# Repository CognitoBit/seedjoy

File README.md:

# SeedJoy

Game-controller firmware for the **Seeed Studio XIAO nRF52840**, with a zero-install web
configurator. The board shows up as a standard HID **joystick** over **USB** or **Bluetooth LE**,
with up to **56 buttons** (74HC165 shift registers) and **4 analog axes**.

> **Board:** Seeed Studio XIAO nRF52840, the *non-Sense* board, using the **"Seeed nRF52 Boards"**
> Arduino core (FQBN `Seeeduino:nrf52:xiaonRF52840`). The mbed-based Seeed core and the Sense
> board definition are not supported by this build.

---

## Features

- **56 buttons** from up to 7 daisy-chained 74HC165s on 3 pins (D6/D7/D8), debounced
- **4 analog axes** (A0–A3, 12-bit) with calibration, deadzone, expo curve, smoothing, invert
- **USB HID or BLE HID**, chosen at boot by pin D9
- **Web configurator** (Chrome/Edge): connect over **Web Serial** (USB cable, either mode) or
  **WebBluetooth** (BLE mode), read and write the full config, calibrate axes, and watch live
  button states
- **Persistent config** in on-chip flash (LittleFS, CRC32-checked)
- **Ghost-input protection**: HID input is held off for 60 s after each BLE connection
- **Battery level** reported through the BLE Battery Service (LiPo on the XIAO's BAT pads)
- Force feedback (USB PID) exists as an experimental, **off-by-default** build option, see
  [docs/ffb-plan.md](docs/ffb-plan.md)

---

## Hardware

### Parts

| Part | Qty | Notes |
|------|-----|-------|
| Seeed Studio XIAO nRF52840 | 1 | Non-Sense |
| 74HC165 shift register | 1–7 | 8 buttons each |
| 10 kΩ resistor | 1 per button | Pull-up on each 74HC165 input |
| Buttons / switches | up to 56 | Input → GND |
| 10 kΩ linear potentiometer | 0–4 | Optional axes |
| Switch or jumper on D9 | 1 | Only to boot into BLE mode |
| 3.7 V single-cell LiPo | 0–1 | Optional, for wireless use |

**Everything runs at 3.3 V.** Power the 74HC165s, pull-ups and pots from the XIAO's **3V3** pin.
XIAO pins are not 5 V tolerant.

### Pin map

| XIAO pin | Port | Function |
|----------|------|----------|
| A0–A3 (D0–D3) | P0.02, P0.03, P0.28, P0.29 | Axes 0–3 (X, Y, Z, Rz), **disabled by default** |
| D4, D5, D10 | P0.04, P0.05, P1.15 | Optional direct GPIO buttons, disabled by default |
| **D6** | P1.11 | 74HC165 **data**: QH (pin 9) of the chip nearest the XIAO |
| **D7** | P1.12 | 74HC165 **clock**: CLK (pin 2) of every chip |
| **D8** | P1.13 | 74HC165 **load**: SH/LD (pin 1) of every chip |
| **D9** | P1.14 | **Mode select**: open = USB, GND at boot = BLE |
| RGB LED | P0.26 red, P0.06 blue | Red: booting / error blinks. Blue: USB mounted, or BLE connected |
| BAT+/BAT− pads | n/a | LiPo (underside) |

### Shift-register wiring (74HC165)

```
            far end                                          nearest XIAO
 3V3 → SER[Chip 1]QH → SER[Chip 2]QH → … → SER[Chip 7]QH ──────────► D6
        buttons 1–8    buttons 9–16          buttons 49–56

 D7 → CLK (pin 2) of every chip        D8 → SH/LD (pin 1) of every chip
 3V3 → VCC (16) of every chip           GND → GND (8) and CLK INH (15) of every chip
```

- Chain with **QH (pin 9) → next chip's SER (pin 10)**. Do not use /QH (pin 7); it's inverted.
- The far-end chip's SER goes to **3V3** (so unused chain positions read as released). Buttons
  1–8 are on that chip: input A = button 1, input H = button 8.
- Each input gets a **10 kΩ pull-up to 3V3**, and the switch goes from the input to **GND**.
  Released reads HIGH, pressed reads LOW. The default *Invert Logic = on* reports pressed as 1.
- Fewer than 7 chips is fine. Set **Number of chips** in the configurator to match what's fitted,
  because numbering always starts at the far-end chip.

Full wiring guide with the 74HC165 pinout: [docs/hardware.md](docs/hardware.md).

**Test board:** a ready-to-fab KiCad board that exercises everything (74HC165 + 8 buttons, chain
header, DIP switches, on-board thumbstick, external analog header) is in [pcb/](pcb/). See
[pcb/README.md](pcb/README.md) for the bring-up checklist and [pcb/BOM.md](pcb/BOM.md) for
India-sourced parts.

---

## Build and flash

### 1. Install the board support package

Arduino IDE 2.x or [arduino-cli](https://arduino.github.io/arduino-cli/latest/installation/).
Add this board-manager URL:

```
https://files.seeedstudio.com/arduino/package_seeeduino_boards_index.json
```

Install **Seeed nRF52 Boards** (tested with **1.1.10**). Do *not* install the "mbed-enabled"
package. No extra libraries are needed: TinyUSB, Bluefruit and LittleFS ship with the core.
Don't install a separate "Adafruit TinyUSB" from Library Manager, since it can shadow the
core's copy.

```bash
arduino-cli config add board_manager.additional_urls \
  https://files.seeedstudio.com/arduino/package_seeeduino_boards_index.json
arduino-cli core update-index
arduino-cli core install Seeeduino:nrf52
```

### 2. Compile

```bash
cd firmware/seedjoy
./compile.sh
```

This produces `build/seedjoy.uf2` (drag-and-drop image), `build/seedjoy.ino.zip` (serial DFU
package) and `build/seedjoy.ino.hex`. `compile.sh` uses `arduino-cli` from your `PATH` (or
`~/bin/arduino-cli`).

In the Arduino IDE: open `firmware/seedjoy/seedjoy.ino`, select **Tools → Board → Seeed nRF52
Boards → Seeed XIAO nRF52840** (not "Sense"), then Upload.

### 3. Flash

**Option A: UF2 drag-and-drop (simplest)**

1. Connect the XIAO by USB-C (use a data cable).
2. **Double-tap the RESET button.** A USB drive appears (the UF2 bootloader).
3. Copy `build/seedjoy.uf2` onto that drive. The board reboots into SeedJoy.

**Option B: serial upload**

```bash
./upload.sh              # finds /dev/cu.usbmodem* (macOS) or /dev/ttyACM* (Linux)
PORT=/dev/cu.usbmodem1101 ./upload.sh   # or pick the port yourself
```

Or in the IDE, press Upload. If the port isn't found, double-tap RESET and retry.

### Apple Silicon Macs without Rosetta

Seeed's core 1.1.10 ships **x86_64-only** `arm-none-eabi-gcc` 9-2019q4 and `adafruit-nrfutil`,
and Arduino's `ctags` is x86_64-only too. Without Rosetta, compiling fails with
`bad CPU type in executable`. Either install Rosetta (`softwareupdate --install-rosetta`), or
point the scripts at native tools:

```bash
# 1. Native ARM toolchain (Arm GNU Toolchain, darwin-arm64 tarball, e.g. 13.3.rel1)
#    https://developer.arm.com/downloads/-/arm-gnu-toolchain-downloads
# 2. adafruit-nrfutil from PyPI
python3 -m venv ~/.venvs/nrfutil && ~/.venvs/nrfutil/bin/pip install adafruit-nrfutil
# 3. Arduino's ctags fork, built natively
git clone --depth 1 --branch 5.8-arduino11 https://github.com/arduino/ctags.git
cd ctags && grep -rl __unused__ . | grep -E '\.(c|h)$' | xargs sed -i '' 's/__unused__/CTAGS_UNUSED/g'
./configure && make && cd ..

# then:
ARM_GCC_BIN=/path/to/arm-gnu-toolchain-13.3.rel1-darwin-arm64-arm-none-eabi/bin \
NRFUTIL=~/.venvs/nrfutil/bin/adafruit-nrfutil \
CTAGS_DIR=/path/to/ctags \
./compile.sh

NRFUTIL=~/.venvs/nrfutil/bin/adafruit-nrfutil ./upload.sh   # or just use the UF2 drive
```

This is how the current tree was build-verified: gcc 13.3.rel1, 148 KB flash (18 %), 20.6 KB RAM
(8 %). The "`_close is not implemented`"-style linker warnings from newer newlib are harmless.

---

## First boot and mode selection

D9 is sampled **once at boot** (internal pull-up):

| D9 at reset | Mode | What the host sees |
|-------------|------|--------------------|
| Nothing connected | **USB** | USB joystick "SeedJoy" + a serial port (VID `0x239A`, PID `0x80F4`) |
| Tied to GND | **BLE** | BLE HID joystick advertising as "SeedJoy" (plus the serial port if USB is plugged in) |

To change mode, change D9 and press RESET. The `mode` field in the saved config is currently
informational only, and D9 always decides.

In USB mode the serial port drops once and reappears about a second after boot. That's expected:
the firmware forces the host to re-enumerate so the joystick interface appears.

Boot log (Serial Monitor, 115200 baud) prints the selected mode, enabled axes and the
shift-register setup.

### Default configuration

| Setting | Default |
|---------|---------|
| Shift registers | **enabled**, 7 chips, D6/D7/D8, Invert Logic **on** |
| Axes 0–3 | **disabled** (enable only the ones you've wired) |
| Direct GPIO buttons | disabled |
| Device name | `SeedJoy` |

With a full 7-chip chain, a board wired as above works with no configuration at all: SR buttons
appear as HID buttons 1–56. With fewer chips, the fitted chips first show up at the top of the
range (one chip on D6 = buttons 49–56) until you set *Number of chips* in the configurator. Nothing
reads as stuck pressed, as long as the far-end SER is tied to 3V3.

> **Upgrading from an older build?** A config already saved on the board keeps its old values.
> In particular the old default was *Invert Logic = off*, which makes every idle button read as
> pressed with pull-up wiring. Open the configurator, **Read from Device**, tick **Invert Logic**,
> and **Write to Device**.

### Testing it

- **Windows:** `joy.cpl` (Game Controllers), select SeedJoy, then Properties
- **Linux:** `jstest /dev/input/js0`
- **Any OS:** https://hardwaretester.com/gamepad in Chrome

`joy.cpl` and browser gamepad testers display **only the first 32 buttons**. The configurator's
Button Mapping tab shows all 64. Games and SDL/DirectInput apps read the full report.

### BLE mode and the 60-second window

Every time a BLE central connects (your PC *or* the web configurator), the firmware holds off
HID input for **60 seconds** so floating or unconfigured inputs can't spam the host while you
configure. The blue LED lights while connected.

- After pairing with your PC, expect **no input for the first minute** of each connection.
- Send `H` over the serial port to enable HID immediately, or `C` to restart the window.
- Press and hold a button on D9 (to GND) during the window to keep it open. A switch left
  closed since boot is ignored for this, so a permanent BLE jumper won't block HID.

Pair from the OS Bluetooth settings as you would any controller. If pairing gets stuck, remove
"SeedJoy" from the OS device list and reset the board.

---

## Web configurator

### Open it

WebBluetooth and Web Serial need a secure context. `http://localhost` counts as one:

```bash
cd configurator
python3 -m http.server 8000
# open http://localhost:8000 in Chrome or Edge (Firefox/Safari have neither API)
```

### Connect

Pick **🔌 USB Serial** or **📡 Bluetooth** at the top, then **Connect Device**.

| Mode | Transport | Works when the firmware is in |
|------|-----------|-------------------------------|
| USB Serial (Web Serial, 115200 baud) | USB cable | USB mode **or** BLE mode (with cable plugged in) |
| Bluetooth (WebBluetooth) | Wireless GATT | BLE mode only |

The Bluetooth picker filters on names starting with `SeedJoy`. If you rename the device, keep
that prefix.

### Workflow

1. **Read from Device** loads the board's current config into the UI. Always do this first.
2. **Pin Config** tab: shift registers (enable, chip count, pins, Invert Logic), axis and GPIO
   button enables.
3. **Axis Calibration** tab: live readout, set min/center/max, deadzone, curve, smoothing.
4. **Button Mapping** tab: 56 indicators light up live as you press buttons. Over serial the
   firmware streams states at 20 Hz; over BLE they arrive as GATT notifications.
5. **Write to Device** saves to flash. Shift-register and axis changes apply immediately, no
   reboot needed.

Pin values in the configurator and in the JSON protocol are **Arduino pin numbers**
(D0–D10 = 0–10); see [docs/protocol.md](docs/protocol.md#pin-numbers).

> ⚠️ Enable only axes and buttons that are physically wired. A floating pin reads noise and
> produces phantom input.

---

## Serial protocol

115200 baud, newline-terminated text commands. Available in both USB and BLE mode.

| Command | Response | Purpose |
|---------|----------|---------|
| `ping` | `{"type":"pong"}` | Connection check |
| `read_config` | `{"type":"config","data":{…}}` | Full config as JSON |
| `write_config:{JSON}` | `{"type":"status","success":true\|false,"message":"…"}` | Apply and save config |
| `stream_buttons` | `{"type":"buttons","data":{"states":[b0,…,b7]}}` at 20 Hz | Start live button stream (8 bytes = 64 bits) |
| `stop_stream` | `{"type":"status",…}` | Stop the button stream |
| `stream_axes` | `{"type":"axes","data":{"raw":[4],"processed":[4]}}` at 20 Hz | Live axis values (the calibration tab uses this over USB) |
| `stop_axes` | `{"type":"status",…}` | Stop the axis stream |
| `C` | text | BLE mode: (re)enter the config window, HID off |
| `H` | text | BLE mode: enable HID now |
| `?` | text | Help |

The BLE GATT config service and message formats are described in [docs/protocol.md](docs/protocol.md).

---

## HID report

One 16-byte input report. Usage page Generic Desktop, usage **Joystick**. Over USB it has no
report ID; over BLE it's Report ID 1.

```
Bytes 0–7    Axes X, Y, Z, Rz   int16 little-endian, −32767 … 32767
Bytes 8–15   Buttons 1–64       1 bit each (SR-only mode uses buttons 1–56)
```

Button bit *n* is HID button *n+1*. In SR-only mode, SR input *n* maps to bit *n*. If any direct
GPIO button is enabled, SR buttons move up by 16 (the 16 GPIO slots come first), so a 7-chip
chain's last 8 buttons no longer fit in the 64-bit report. For 56 buttons, use SR only.

---

## Troubleshooting

**Every button shows as pressed.** Invert Logic is off (a config saved by an older build). Read →
tick *Invert Logic* → Write.

**Buttons shifted / wrong numbers.** The configured chip count doesn't match the chips fitted, or
the chain is wired through /QH (pin 7) instead of QH (pin 9).

**No shift-register buttons at all.** Check D6/D7/D8 and 3V3/GND to every chip, CLK INH (pin 15)
to GND, and SR *enabled* in the config. The boot log prints the SR settings. Configs written by
older configurator builds stored invalid pin numbers (e.g. 43/44/45 for D6/D7/D8). The firmware
now repairs these at boot and logs `Repaired invalid pin numbers in stored config`.

**USB mode: no joystick, only a serial port.** Use a data cable, and check the boot log says
`USB HID initialized successfully`. On Windows, look in `joy.cpl`, not only Device Manager.

**BLE mode: connected but no input.** Wait out the 60 s window, or send `H` over serial.

**Can't find the device in the Bluetooth picker.** Check D9 was on GND at reset (the boot log
says `Selected mode: BLE`), and that the name still starts with `SeedJoy`.

**Axes drift or jitter.** Calibrate, raise the deadzone or smoothing, add 100 nF from wiper to GND.

**Config lost after reboot.** After a write the log should say `Config saved to Flash`; on the next boot, `Config loaded from Flash`. Anything else (`CRC mismatch`, `size mismatch`) means the stored config was rejected and defaults were used.

**Compile fails with `bad CPU type in executable`.** See
[Apple Silicon Macs without Rosetta](#apple-silicon-macs-without-rosetta).

More: [docs/troubleshooting.md](docs/troubleshooting.md).

---

## Project layout

```
firmware/seedjoy/
├── seedjoy.ino          setup/loop, D9 mode select, BLE config window, serial commands
├── config.h             DeviceConfig struct, default pins
├── axes.*               ADC read, calibration, deadzone, curves, smoothing
├── buttons.*            GPIO + shift-register buttons, debounce, 64-bit state
├── shift_registers.*    74HC165 bit-bang reader
├── usb_hid.*            TinyUSB joystick (16-byte report)
├── ble_hid.*            Bluefruit BLE HID joystick + battery service
├── ble_config.*         GATT config / monitor / calibration service
├── storage.*            LittleFS config persistence, CRC32
├── ffb_*                Experimental force feedback (ENABLE_FFB=0 by default)
├── compile.sh / upload.sh
firmware/tests/          Host-side unit tests for the FFB engine (bash run_tests.sh)
configurator/            Static web app: index.html, app.js, serial.js, ble.js, config.js, …
docs/                    hardware.md, protocol.md, troubleshooting.md, getting-started.md, FFB docs
```

---

## Status and known limitations

- The current tree **compiles** for `Seeeduino:nrf52:xiaonRF52840` (core 1.1.10) and the host
  unit tests pass. The fixes in this revision (USB re-enumeration, LED polarity, D9 handling,
  configurator pin numbering, SR polarity default, stored-pin repair) have **not yet been verified on a physical
  board**.
- BLE config characteristics are unauthenticated (anyone in range can write config). See
  [docs/audit.md](docs/audit.md) H2.
- `mode` in the config is ignored (D9 decides), and `autoSleep` isn't implemented yet.
- Mixing GPIO buttons with a full 7-chip chain drops the last 8 SR buttons (see HID report).

## Roadmap

- [ ] Configuration import/export as a JSON file
- [ ] Rotary encoders
- [ ] 8 axes via external ADC (ADS1115)
- [ ] Button matrices
- [ ] OTA firmware update via BLE DFU

## License

MIT, see [LICENSE](LICENSE).

## Credits

Inspired by [FreeJoy](https://github.com/FreeJoy-Team/FreeJoy) by Alexandr Yaroshenko.

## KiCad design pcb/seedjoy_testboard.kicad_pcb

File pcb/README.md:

# SeedJoy Test Board rev A: bring-up checklist

Board: `seedjoy_testboard.kicad_pro` (KiCad 10). Fab files: `seedjoy_testboard_gerbers.zip`.
Parts: [BOM.md](BOM.md), with jumper settings.

## Before ordering the PCB

- [ ] Buy the KY-023 / PS2 joystick module first. Desolder the stick and measure it: the 3 pins of
      each pot are **2.5 mm apart**, and the two pot rows are **8.73 mm from the stick centre**
      (Alps RKJXV1224005 pattern). If your clone differs, stop and report it before ordering.
- [ ] **1:1 paper-fit test** (catches a mirrored pattern and body pegs that calipers miss):
      in KiCad, File → Print F.Cu + Edge.Cuts at **100 % scale** and check the board width
      (130 mm) with a ruler. Push the desoldered stick's legs through the printed pads (from the
      printed side, stick on top). It must sit **flat**: no plastic pegs hitting the paper, and
      the X-pot row on top, the Y-pot column on the right, the switch legs at the bottom. The legs
      should protrude ≥ 2.4 mm below the body to solder through a 1.6 mm board.
      Repeat for the DIP switch, one tactile switch, RN1 and the XIAO socket pitch.

## Before powering up (bare board, multimeter)

- [ ] **3V3 to GND is not a short**: > 1 kΩ on the J2 3V3 pin vs GND.
- [ ] No XIAO fitted yet. Check continuity **J2 pin 3 (3V3) → U1 socket pin 16** and
      **J2 pin 2 (GND) → U1 socket pin 8**.

## Assembly order

1. IC socket (notch towards the XIAO side of the silkscreen), RN1 (dot = pin 1 = square pad), R1, C1.
2. DIP switch (switch 1 next to the "1 D4" label), 8 tactile switches.
3. Female headers: J1/J2 (XIAO), J3 (external analog). Male headers: J4, J5, J6, J7, J8, J9.
4. Thumbstick U2 last. Insert the **74HC165** into its socket, notch matching.
5. Plug in the XIAO **with USB-C towards the top edge** ("USB up" silkscreen).

## First power-up (no jumpers fitted, all DIP switches OFF)

1. Flash firmware: double-tap RESET → `XIAO-BOOT` drive → copy `firmware/seedjoy/build/seedjoy.uf2`.
2. After about 1 s the **blue LED is on** and the red LED is off (USB HID mounted). A red LED
   blinking 5× means USB HID failed.
3. The OS lists a game controller named **SeedJoy** (`joy.cpl` on Windows, `jstest` on Linux).
4. The serial port drops and reappears once at boot (USB re-enumeration), so a terminal usually
   misses the boot log. Open it afterwards and send `?`: the command help confirms the firmware
   is alive.

## Configure (configurator → USB Serial → Connect → **Read from Device**)

- [ ] **Pin Config → Number of chips = 1**, Invert Logic **ticked** → **Write to Device**.
      (The firmware default is 7 chips. With 7, this board's buttons show up as HID 49–56.)
- [ ] **Button Mapping** tab: BTN1…BTN8 light up as indicators 1…8. Idle = all dark.
      Use this tab as the ground truth. **Windows `joy.cpl` and browser gamepad testers only
      show the first 32 buttons**, so at the default 7 chips (HID 49–56) the board would look dead
      there. That's another reason to set chips = 1 first.

## Analog

1. Fit **J8 on 1-2** (X from the on-board stick) and **J4 on row 1** (X → A0).
   Fit **J9 on 1-2** and **J5 on row 2** (Y → A1). *Never put J4 and J5 on the same row.*
2. Pin Config: enable **Axis 0** (pin A0) and **Axis 1** (pin A1) → Write.
3. Axis Calibration: raw ≈ 2048 at rest. PS2-style sticks usually **don't reach 0 / 4095** at
   the ends (often ~300–3800). That's normal, and the calibration exists for it:
   run min/center/max → Write.
4. External sensor: move J8 (or J9) to **2-3**, plug the sensor into **J3** (GND, 3V3, X, Y, SW).
   **3.3 V only.** Use a 3.3 V-capable hall sensor (e.g. SS49E / DRV5055A1 at 3.3 V).
5. **J6 on** means the stick push button (on-board or J3 SW) acts as BTN8.

## GPIO buttons and mode (DIP switch SW9)

- [ ] Enable GPIO buttons 0–2 (pins D4, D5, D10) in the configurator → Write. DIP 1–3 ON = pressed.
      **While any GPIO button is enabled, the shift-register buttons move to HID 17+.**
- [ ] **DIP 4 ON + reset** boots BLE mode (`Selected mode: BLE`). Pair "SeedJoy" from the OS.
      Input starts **60 s after each connection** (send `H` over serial to skip).
      DIP 4 back OFF + reset returns to USB mode.

## Chaining your own 74HC165 board (J7)

J7 = 3V3, GND, CLK (D7), LOAD (D8), SER-in. Your chain's last QH → J7 pin 5.
Your N chips become HID 1…8N and this board's buttons follow. Set Number of chips = N + 1.

## Known cosmetic warnings in KiCad

The DRC shows `lib_footprint_mismatch` (library metadata) and 3 "field differs" parity notes.
They don't affect fabrication. Tools → Update Footprints from Library / Update PCB from
Schematic clears them.

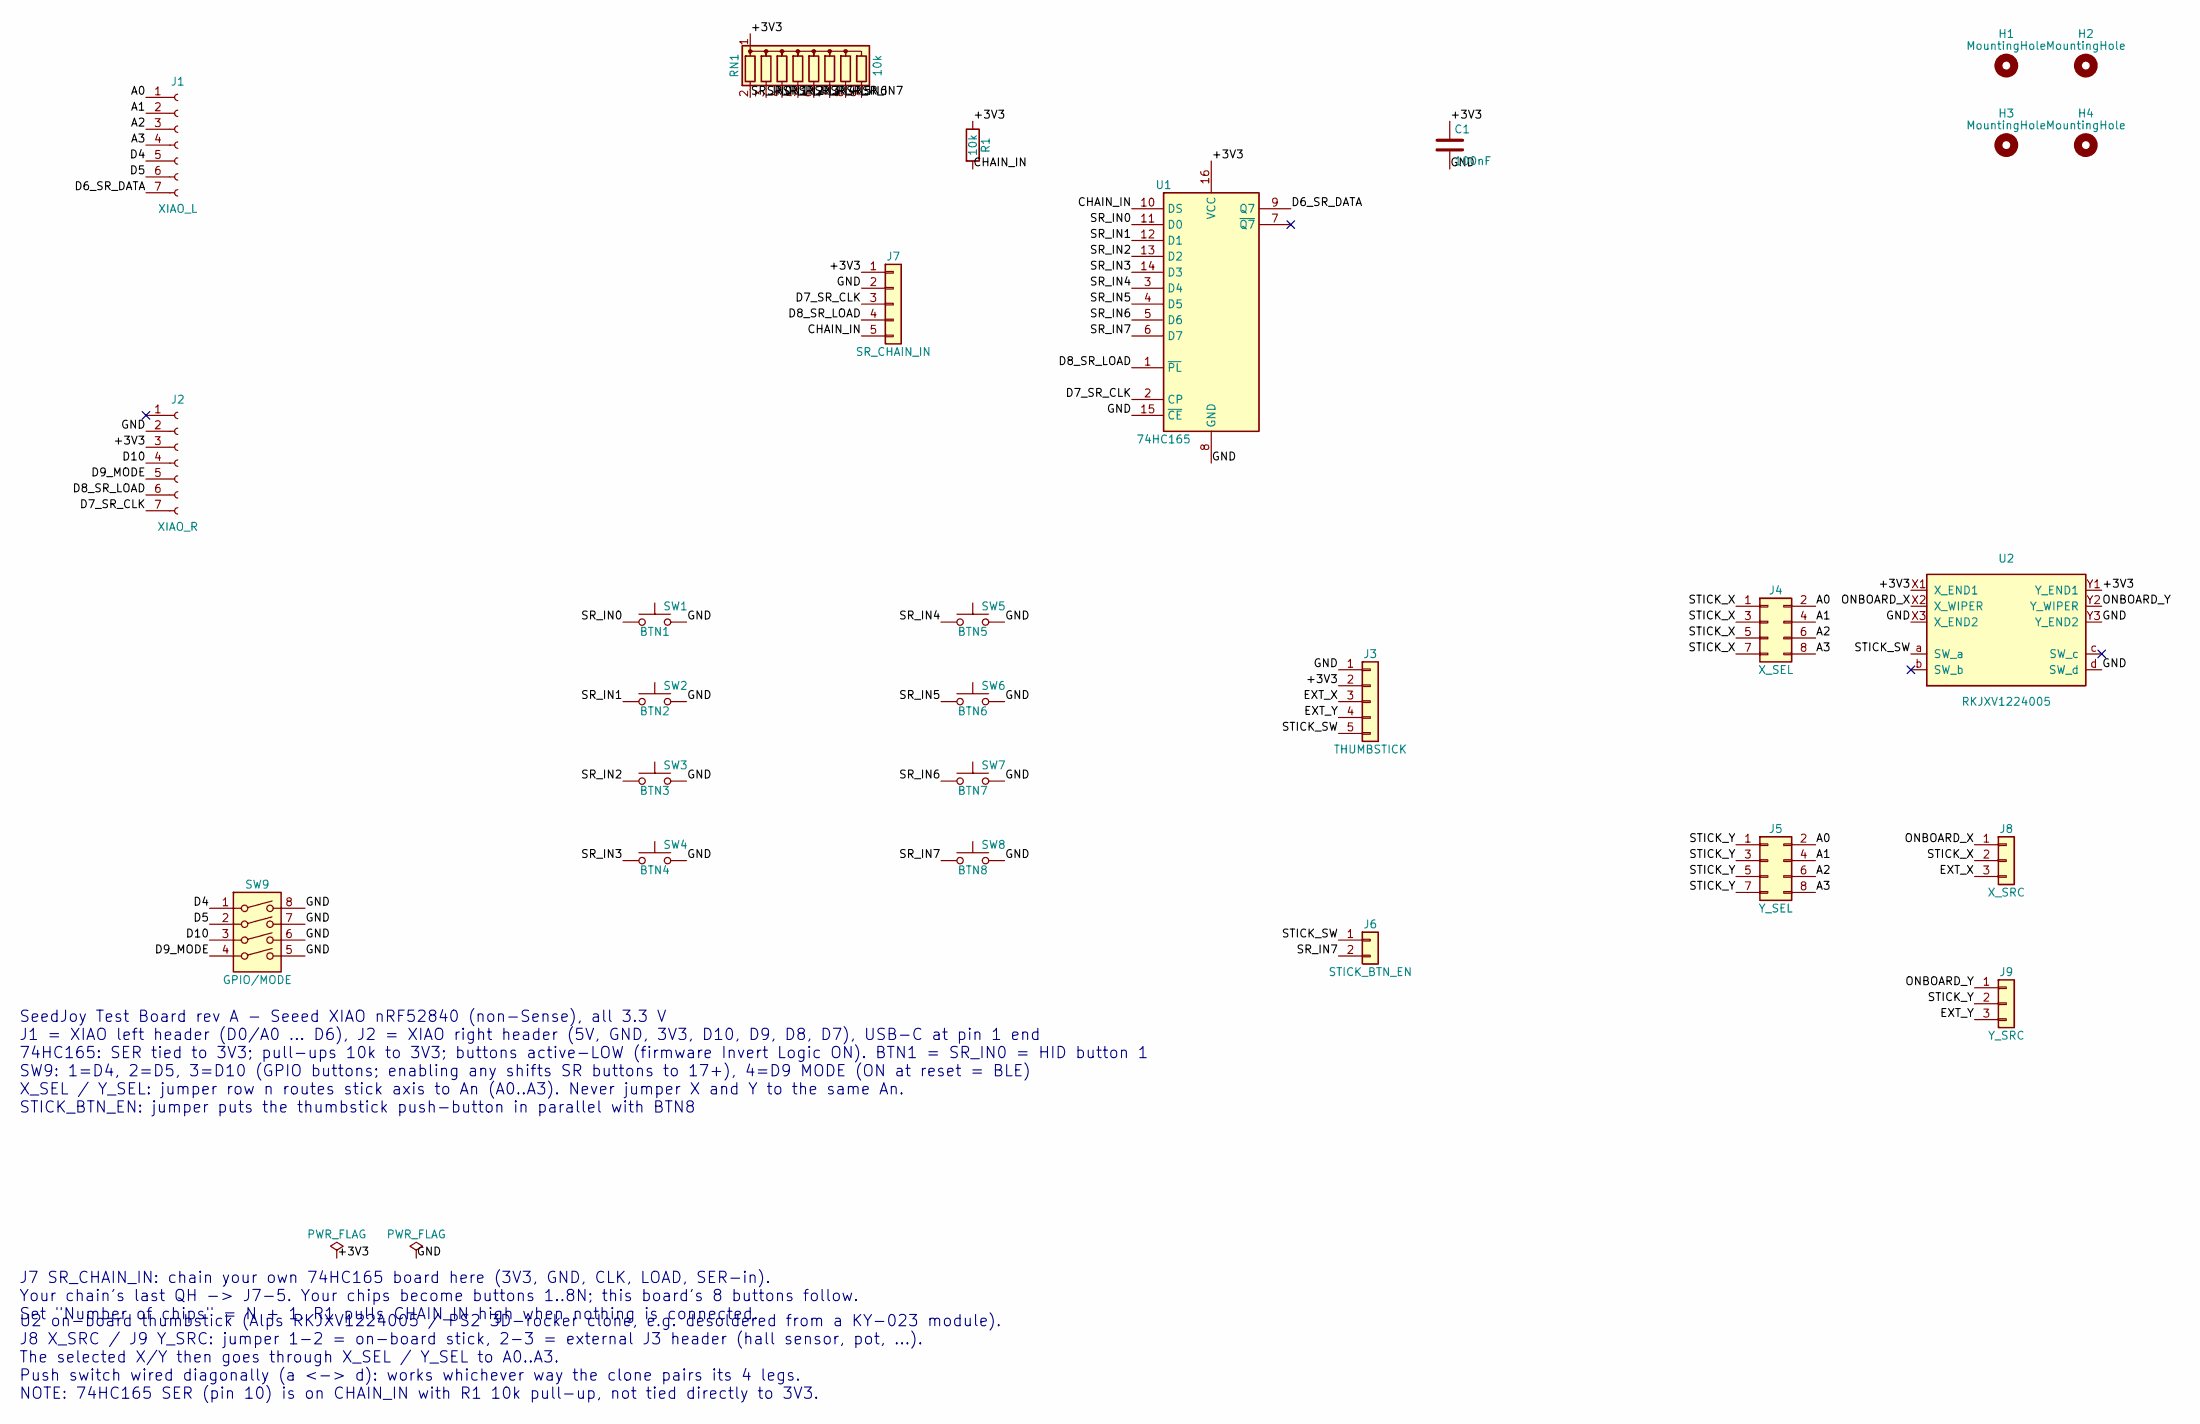
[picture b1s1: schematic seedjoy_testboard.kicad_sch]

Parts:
C1: 100nF; C_Disc_D5.0mm_W2.5mm_P5.00mm
H1, H2, H3, H4: MountingHole; MountingHole_3.2mm_M3
J1: XIAO_L; PinSocket_1x07_P2.54mm_Vertical
J2: XIAO_R; PinSocket_1x07_P2.54mm_Vertical
J3: THUMBSTICK; PinHeader_1x05_P2.54mm_Vertical
J4: X_SEL; PinHeader_2x04_P2.54mm_Vertical
J5: Y_SEL; PinHeader_2x04_P2.54mm_Vertical
J6: STICK_BTN_EN; PinHeader_1x02_P2.54mm_Vertical
J7: SR_CHAIN_IN; PinHeader_1x05_P2.54mm_Vertical
J8: X_SRC; PinHeader_1x03_P2.54mm_Vertical
J9: Y_SRC; PinHeader_1x03_P2.54mm_Vertical
R1: 10k; R_Axial_DIN0207_L6.3mm_D2.5mm_P10.16mm_Horizontal
RN1: 10k; R_Array_SIP9
SW1: BTN1; SW_PUSH_6mm_H5mm
SW2: BTN2; SW_PUSH_6mm_H5mm
SW3: BTN3; SW_PUSH_6mm_H5mm
SW4: BTN4; SW_PUSH_6mm_H5mm
SW5: BTN5; SW_PUSH_6mm_H5mm
SW6: BTN6; SW_PUSH_6mm_H5mm
SW7: BTN7; SW_PUSH_6mm_H5mm
SW8: BTN8; SW_PUSH_6mm_H5mm
SW9: GPIO/MODE; SW_DIP_SPSTx04_Slide_9.78x12.34mm_W7.62mm_P2.54mm
U1: 74HC165; DIP-16_W7.62mm_Socket
U2: RKJXV1224005; Alps_RKJXV1224005_Thumbstick

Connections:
/+3V3: C1.1, J2.3, J3.2, J7.1, R1.1, RN1.1 (common), U1.16 (VCC), U2.X1 (X_END1), U2.Y1 (Y_END1)
/A0: J1.1, J4.2, J5.2
/A1: J1.2, J4.4, J5.4
/A2: J1.3, J4.6, J5.6
/A3: J1.4, J4.8, J5.8
/CHAIN_IN: J7.5, R1.2, U1.10 (DS)
/D4: J1.5, SW9.1
/D5: J1.6, SW9.2
/D6_SR_DATA: J1.7, U1.9 (Q7)
/D7_SR_CLK: J2.7, J7.3, U1.2 (CP)
/D8_SR_LOAD: J2.6, J7.4, U1.1 (~PL)
/D9_MODE: J2.5, SW9.4
/D10: J2.4, SW9.3
/EXT_X: J3.3, J8.3
/EXT_Y: J3.4, J9.3
/GND: C1.2, J2.2, J3.1, J7.2, SW1.2, SW2.2, SW3.2, SW4.2, SW5.2, SW6.2, SW7.2, SW8.2, SW9.5, SW9.6, SW9.7, SW9.8, U1.8 (GND), U1.15 (~CE), U2.X3 (X_END2), U2.Y3 (Y_END2), U2.d (SW_d)
/ONBOARD_X: J8.1, U2.X2 (X_WIPER)
/ONBOARD_Y: J9.1, U2.Y2 (Y_WIPER)
/SR_IN0: RN1.2 (R1), SW1.1, U1.11 (D0)
/SR_IN1: RN1.3 (R2), SW2.1, U1.12 (D1)
/SR_IN2: RN1.4 (R3), SW3.1, U1.13 (D2)
/SR_IN3: RN1.5 (R4), SW4.1, U1.14 (D3)
/SR_IN4: RN1.6 (R5), SW5.1, U1.3 (D4)
/SR_IN5: RN1.7 (R6), SW6.1, U1.4 (D5)
/SR_IN6: RN1.8 (R7), SW7.1, U1.5 (D6)
/SR_IN7: J6.2, RN1.9 (R8), SW8.1, U1.6 (D7)
/STICK_SW: J3.5, J6.1, U2.a (SW_a)
/STICK_X: J4.1, J4.3, J4.5, J4.7, J8.2
/STICK_Y: J5.1, J5.3, J5.5, J5.7, J9.2

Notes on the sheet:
SeedJoy Test Board rev A - Seeed XIAO nRF52840 (non-Sense), all 3.3 V J1 = XIAO left header (D0/A0 ... D6), J2 = XIAO right header (5V, GND, 3V3, D10, D9, D8, D7), USB-C at pin 1 end 74HC165: SER tied to 3V3; pull-ups 10k to 3V3; buttons active-LOW (firmware Invert Logic ON). BTN1 = SR_IN0 = HID bu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
J7 SR_CHAIN_IN: chain your own 74HC165 board here (3V3, GND, CLK, LOAD, SER-in). Your chain's last QH -> J7-5. Your chips become buttons 1..8N; this board's 8 buttons follow. Set "Number of chips" = N + 1. R1 pulls CHAIN_IN high when nothing is connected.
U2 on-board thumbstick (Alps RKJXV1224005 / PS2 3D-rocker clone, e.g. desoldered from a KY-023 module). J8 X_SRC / J9 Y_SRC: jumper 1-2 = on-board stick, 2-3 = external J3 header (hall sensor, pot, ...). The selected X/Y then goes through X_SEL / Y_SEL to A0..A3. Push switch wired diagonally (a <->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

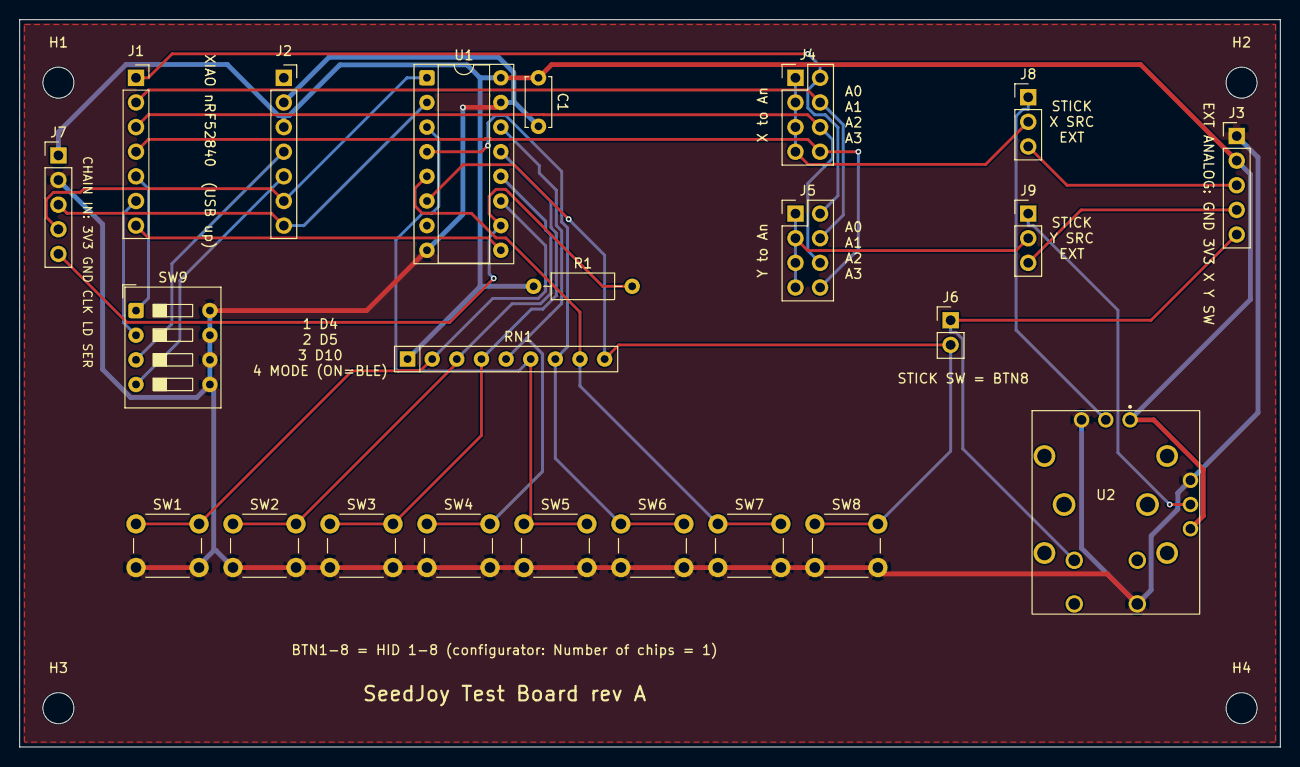
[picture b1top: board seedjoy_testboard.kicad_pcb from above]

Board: 2 copper layers, 130.0 x 75.0 mm, 27 parts (0 on the bottom side), 29 nets.

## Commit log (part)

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2026-02-16 feat: real-time button monitoring (firmware + configurator UI)
2026-02-16 chore: add .gitignore
2026-02-17 fix: prevent floating pin chaos - disable all inputs by default
    BREAKING CHANGE: All axes and buttons are now disabled by default for safety.
    Users must explicitly enable inputs in the configurator after connecting hardware.
    Changes:
    - Disable all axes/buttons in default config (config.h)
    - Extend BLE config timeout from 10s to 60s
    - Add safety gate in sendHIDReports() to block output during config mode
2026-02-17 feat: add enable/disable controls to configurator UI
    - Add checkbox to enable/disable each axis and button
    - Add 'Enable All' / 'Disable All' bulk buttons for axes and buttons
    - Pin selectors are disabled when input is unchecked
    - Add safety notice warning about floating pins
    - Update default config to match firmware (all disabled by default)
    - Add CSS styling for new UI elements
2026-02-17 fix: initialize BLE config service before advertising
    The config service was being initialized AFTER BLE advertising started,
    which meant the service UUID wasn't included in the advertising packet.
    This caused the configurator to fail to discover the config service
    characteristics (read/write/monitor).
    Changes:
    - Remove auto-start of advertising from bleHID.begin()
2026-02-17 fix: disable BLE bonding and add debug logging for config service
    - Disable BLE security/bonding (setIOCaps false, clearBonds)
    - Prevents OS pairing cache issues requiring device forget/re-pair
    - Add Serial debug output for config service UUID
    - HID devices don't need pairing security
2026-02-17 fix: remove clearBonds() call - method doesn't exist in Bluefruit library
    setIOCaps(false, false, false) is sufficient to disable bonding
2026-02-17 fix: add config service UUID to BLE advertising packet
    - Include config service UUID in advertising packet
    - WebBluetooth requires services in optionalServices to be advertised
    - Without this, getPrimaryService() fails with service not found
    - Fixes 'Configuration service not available' error
2026-02-17 fix: properly add config service to BLE advertising using addService()
    - Changed startAdvertising() to accept BLEService* parameter
    - Use addService() with config service reference instead of addUuid() with string
    - String literals don't work with addUuid() - causes silent failure
    - Pass &bleConfig.getService() from main sketch
    - This ensures config service UUID is properly advertised for WebBluetooth discovery
    - Fixes root cause of 'Configuration service not available' error
2026-02-17 debug: add detailed logging for BLE service discovery
    - Add console logging in configurator to track service/characteristic discovery
    - Add Serial logging in firmware for service initialization and advertising
    - Log whether config service is added to scan response
    - This will help identify exactly where discovery fails
2026-02-17 fix: remove service.started() call - method doesn't exist
2026-02-17 fix: move config service to main advertising packet
    - WebBluetooth may not discover services only in scan response
    - Move config service from scan response to main advertising packet
    - Move device name to scan response only to save space
    - Both HID and config services now in main advertising for reliable discovery
2026-02-17 debug: add characteristic initialization logging and fix button parsing
    - Add debug output for characteristic initialization success/failure
    - Fix DataView buffer offset bug in button data parsing
    - Restore service.begin() before characteristic.begin() order
    - Will help identify why characteristics aren't discovered
2026-02-17 fix: remove extra closing brace causing compilation error
2026-02-17 fix: add size validation to button parsing and better error logging
    - Add byteLength check before parsing button data to prevent RangeError
    - Add try/catch with error messages for characteristic discovery
    - Will show exact error why Read/Write characteristics aren't found
2026-02-17 fix: rate limit mode button logs and add clearer BLE init markers
    - Only log mode button held once per second instead of every loop
    - Add prominent section markers for BLE initialization
    - Makes it easier to see characteristic initialization results
    - Prevents serial monitor flooding
2026-02-17 fix: use dataView directly instead of buffer in axis parsing
    - Same buffer offset bug as button parsing
    - Use dataView parameter directly to preserve byteOffset
    - Add size validation to axis data parsing
    - Prevents RangeError in axis data handler
2026-02-17 fix: initialize characteristics BEFORE service.begin()
    CRITICAL FIX: Bluefruit requires characteristics to be configured and begun
    BEFORE calling service.begin(), otherwise they don't get added to the service.
    This is why WebBluetooth couldn't find any characteristics - they weren't
    in the service! The service existed but was empty.
    Correct order:
    1. characteristic.begin() for all characteristics
2026-02-17 feat: add WebSerial support with dual-mode connection toggle
    - Created serial.js for WebSerial communication (USB alternative to BLE)
    - Added connection mode toggle UI (Bluetooth/USB Serial buttons)
    - Updated app.js to support both BLE and Serial connections
    - Added CSS styling for mode selector
    - Enhanced firmware serial command handler for line-based commands
    - Added serial commands: read_config, write_config:{JSON}, ping
2026-02-17 fix: correct pin configuration for XIAO nRF52840
    Critical fixes based on official Seeed Studio pinmap:
    - Move MODE_SELECT_PIN from D0 to D9 (D0 conflicts with A0)
    - Define shift register pins: D6 (data), D7 (clock), D8 (load)
    - Minimize default button pins to D4, D5, D10 (rest disabled)
    - Update ShiftRegisterConfig defaults to use D6/D7/D8
    - Add detailed pin comments with chip pin numbers
2026-02-17 fix: update configurator UI with correct XIAO nRF52840 pin mappings
    Updates to match firmware pin configuration changes:
    Configurator UI (config.js):
    - Update default button pins to D4, D5, D10 (rest disabled as 0xFF)
    - Set shift register defaults to D6 (0x2B), D7 (0x2C), D8 (0x2D)
    - Fix getAvailablePins() with correct XIAO pin mappings:
    * D0-D3 as A0-A3 (analog axes)
2026-02-21 SR ready
2026-02-21 ble fix WIP
2026-04-23 write config added
